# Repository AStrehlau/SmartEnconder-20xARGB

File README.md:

# SmartEncoder-20xARGB

This "SmartEncoder" uses 20 adressable LEDs (SK6805-EC15 or potentially XL-1615RGBC-WS2812B) to visualize the set point of the encoder. The SmartEncoder boasts WiFi and Bluetooth capability using the ESP32, which makes it viable for Smart Home and PC control applications.<br>
It should be noted that stock Windows does not normally have the capability to send the current volume level over BT, which is why a PC side software to take care of that will be uploaded  in the future for use as a BT PC volume knob.

## Hardware

You can directly order the three PCBs needed for this project using the Gerber files (generated for JLCPCB but likely to work with most common providers) or modify the PCB files at your discretion and generate new Gerber files.

Each of the three PCBs have to be completely assembled before they can be stacked in the correct order using the 3D printed spacers and either wire or very long headers. For the assembly of the Top/LED PCB it is recommended if not necessary to order a stencil with the PCBs. The other PCBs can be assembled without one if so desired.

There is a complete BOM (except the very long headers/wire and M3x25m screws!) for all three PCBs and an interactive BOM for the PCB with the ESP32 on it. There is no ibom for the other two PCBs since every capacitor used on them is 100nF, every resistor on the encoder PCB is 10k and the one resistor on the LED PCB is 330R as can be seen in the schematics.<br>
The EMI filter on the ESP32 PCB (L1, L2 and C4) can be left out and Jumper JP1 soldered instead, although it is not recommended. Doing this has no effect on the functionality.<br>
Especially if you don't plan on running intensive animations on the LEDs the 20 bypass capacitors are definitely overkill (even though the datasheet might disagree). If you want to save on parts/ time spent placing them you can just place C14, C15 and C16 which was more than enough in my testing even just one of them might work for you.

## 3D printed case

Thanks to [Nedos on Thingiverse](https://www.thingiverse.com/thing:6506406) designing a case including two knob versions for you to choose from and anti-bleed part for this project you can simply download the files and print them.<br>
The holes in the knob are meant to be filled with regular 1.75mm diameter transparent filament and either both surfaces cut flush using a side cutter or even sanded down for a better look.<br>
The anti-bleed part can simply be put on the LEDs making sure not to damage them.<br>
For assembly you only need the printed parts including spacers and M3x25mm screws, preferably with a flat underside.

## Software 

Because of layout reasons the LEDs have to be addressed in the opposite than expected order (LED number on the silkscreen is correct) which can result in longer code depending on the application.

There is a demo code for the LEDs which is just a slightly modified version of the Adafruit NEOPIXEL "strandtest" example to check if the LEDs are soldered correctly and undamaged as well as to give you a nice lightshow as can be seen at the top.<br>
This code can be flashed onto the ESP32 using the Arduino IDE.

Also available is a ESPHome configuration to integrate the SmartEncoder into HomeAssistant.

WIP: Code for ESP and PC to communicate via Serial over Bluetooth to use as a volume knob with accurate volume display on the SmartEncoder side

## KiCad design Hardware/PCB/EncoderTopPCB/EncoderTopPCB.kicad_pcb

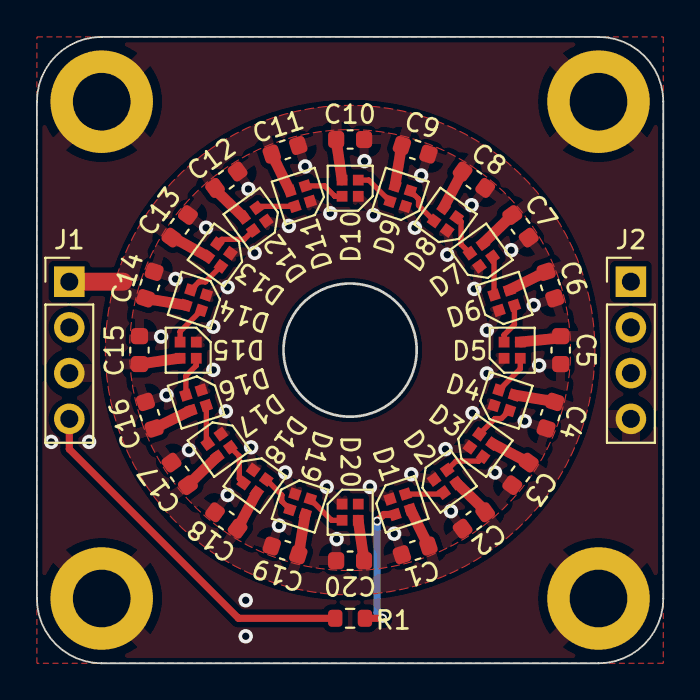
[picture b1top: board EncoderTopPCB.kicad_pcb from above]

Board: 2 copper layers, 34.8 x 34.8 mm, 47 parts (0 on the bottom side), 23 nets.

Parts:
C1, C2, C3, C4, C5, C6, C7, C8, C9, C10, C11, C12, C13, C14, C15, C16, C17, C18, C19, C20: 10V/100nF/X7R; C_0603_1608Metric
D1, D2, D3, D4, D5, D6, D7, D8, D9, D10, D11, D12, D13, D14, D15, D16, D17, D18, D19, D20: SK6805; SK6805-EC15
H1, H2, H3, H4: DNP; MountingHole_3.2mm_M3_ISO7380_Pad
J1, J2: DNP; PinHeader_1x04_P2.54mm_Vertical
R1: 330R; R_0603_1608Metric

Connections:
+5V: C1.1, C2.1, C3.1, C4.1, C5.1, C6.1, C7.1, C8.1, C9.1, C10.1, C11.1, C12.1, C13.1, C14.1, C15.1, C16.1, C17.1, C18.1, C19.1, C20.1, D1.2 (VDD), D2.2 (VDD), D3.2 (VDD), D4.2 (VDD), D5.2 (VDD), D6.2 (VDD), D7.2 (VDD), D8.2 (VDD), D9.2 (VDD), D10.2 (VDD), D11.2 (VDD), D12.2 (VDD), D13.2 (VDD), D14.2 (VDD), D15.2 (VDD), D16.2 (VDD), D17.2 (VDD), D18.2 (VDD), D19.2 (VDD), D20.2 (VDD), J1.1
GND: C1.2, C2.2, C3.2, C4.2, C5.2, C6.2, C7.2, C8.2, C9.2, C10.2, C11.2, C12.2, C13.2, C14.2, C15.2, C16.2, C17.2, C18.2, C19.2, C20.2, D1.4 (VSS), D2.4 (VSS), D3.4 (VSS), D4.4 (VSS), D5.4 (VSS), D6.4 (VSS), D7.4 (VSS), D8.4 (VSS), D9.4 (VSS), D10.4 (VSS), D11.4 (VSS), D12.4 (VSS), D13.4 (VSS), D14.4 (VSS), D15.4 (VSS), D16.4 (VSS), D17.4 (VSS), D18.4 (VSS), D19.4 (VSS), D20.4 (VSS), H1.1, H2.1, H3.1, H4.1, J1.3, J2.4
IO3: J1.4, R1.1
unnamed: D1.1 (DIN), R1.2
unnamed: D1.3 (DOUT), D2.1 (DIN)
unnamed: D2.3 (DOUT), D3.1 (DIN)
unnamed: D3.3 (DOUT), D4.1 (DIN)
unnamed: D4.3 (DOUT), D5.1 (DIN)
unnamed: D5.3 (DOUT), D6.1 (DIN)
unnamed: D6.3 (DOUT), D7.1 (DIN)
unnamed: D7.3 (DOUT), D8.1 (DIN)
unnamed: D8.3 (DOUT), D9.1 (DIN)
unnamed: D9.3 (DOUT), D10.1 (DIN)
unnamed: D10.3 (DOUT), D11.1 (DIN)
unnamed: D11.3 (DOUT), D12.1 (DIN)
unnamed: D12.3 (DOUT), D13.1 (DIN)
unnamed: D13.3 (DOUT), D14.1 (DIN)
unnamed: D14.3 (DOUT), D15.1 (DIN)
unnamed: D15.3 (DOUT), D16.1 (DIN)
unnamed: D16.3 (DOUT), D17.1 (DIN)
unnamed: D17.3 (DOUT), D18.1 (DIN)
unnamed: D18.3 (DOUT), D19.1 (DIN)
unnamed: D19.3 (DOUT), D20.1 (DIN)

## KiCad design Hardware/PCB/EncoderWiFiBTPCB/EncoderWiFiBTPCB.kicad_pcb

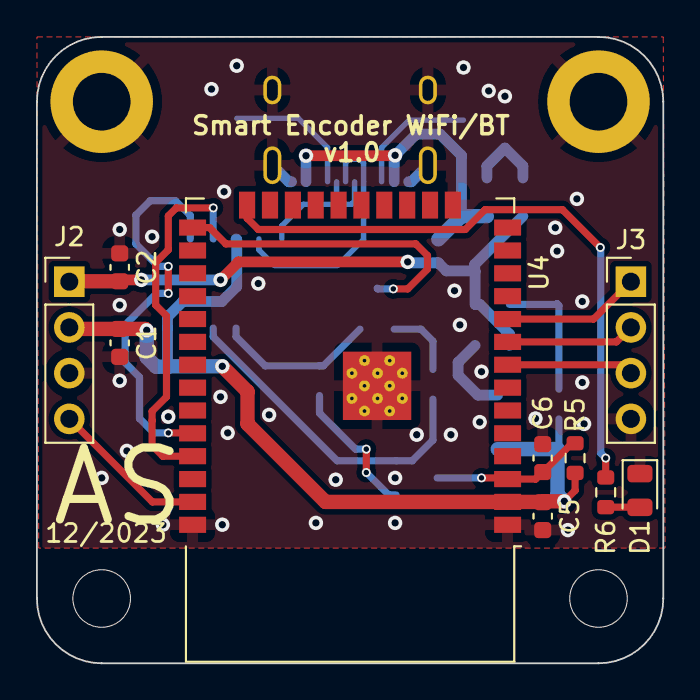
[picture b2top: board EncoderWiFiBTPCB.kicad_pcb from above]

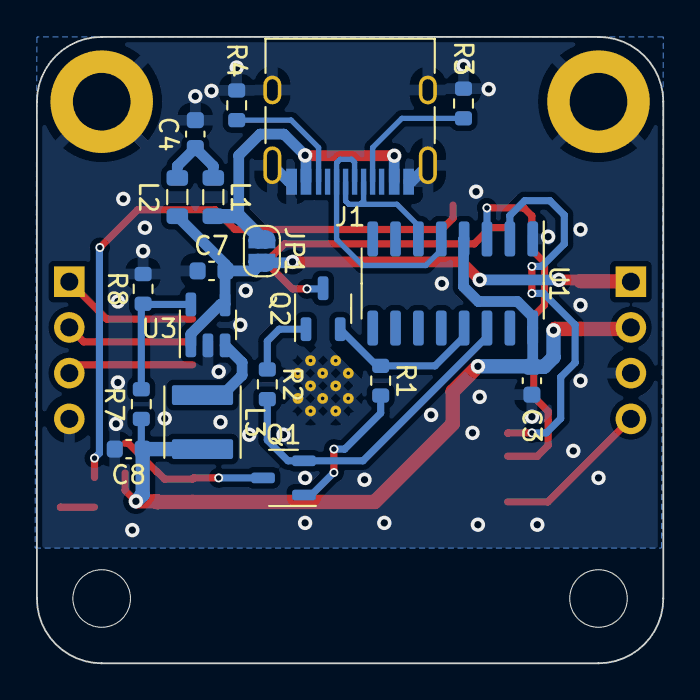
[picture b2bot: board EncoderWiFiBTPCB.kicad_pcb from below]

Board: 2 copper layers, 34.8 x 34.8 mm, 33 parts (19 on the bottom side), 25 nets.

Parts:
C1, C2, C4: 1uF/25V/X5R; C_0603_1608Metric
C3, C5, C6: 100nF/10V/X7R; C_0603_1608Metric
C7, C8: 22uF/10V/X5R; C_0603_1608Metric
D1: BLUE; LED_0805_2012Metric
H1, H2: MountingHole_Pad; MountingHole_3.2mm_M3_ISO7380_Pad
H3, H4: MountingHole; MountingHole_3.2mm_M3_ISO7380
J1: USB_C_Receptacle_USB2.0; USB_C_Receptacle_HRO_TYPE-C-31-M-12
J2, J3: Conn_01x04_Pin; PinHeader_1x04_P2.54mm_Vertical
JP1: SolderJumper_2_Open; SolderJumper-2_P1.3mm_Open_RoundedPad1.0x1.5mm
L1, L2: WLBD2012HCU601TH; L_0805_2012Metric
L3: 2.2uH; L_Abracon_ASPI-4030S
Q1, Q2: MMBT4401; SOT-23-3
R1, R2, R5: 10k; R_0603_1608Metric
R3, R4: 5.1k; R_0603_1608Metric
R6: 1k; R_0603_1608Metric
R7: 68k; R_0603_1608Metric
R8: 15k; R_0603_1608Metric
U1: CH340C; SOIC-16_3.9x9.9mm_P1.27mm
U3: M3406; SOT-23-5
U4: ESP32-WROOM-32D

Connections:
+3V3: C1.1, C3.1, C5.2, C8.1, J2.2, L3.2, R5.2, R7.1, U1.4 (V3), U1.16 (VCC), U4.2 (VDD)
+5V: C2.1, C7.1, J2.1, JP1.2 (B), L2.2, U3.1 (RUN), U3.4 (VIN)
D+: J1.A6 (D+), J1.B6 (D+), U1.5 (UD+)
D-: J1.A7 (D-), J1.B7 (D-), U1.6 (UD-)
ENCODER_A: J3.2, U4.9 (IO33)
ENCODER_B: J3.3, U4.8 (IO32)
ENCODER_BTN: J3.1, U4.10 (IO25)
GND: C1.2, C2.2, C3.2, C4.2, C5.1, C6.1, C7.2, C8.2, D1.1 (K), H1.1, H2.1, J1.A1 (GND), J1.A12 (GND), J1.B1 (GND), J1.B12 (GND), J1.S1 (SHIELD), J2.3, J3.4, R3.2, R4.2, R8.2, U1.1 (GND), U3.2 (GND), U4.1 (GND), U4.15 (GND), U4.38 (GND), U4.39 (GND)
IO23: J2.4, U4.37 (IO23)
unnamed: C4.1, L1.2, L2.1
unnamed: D1.2 (A), R6.1
unnamed: J1.A5 (CC1), R3.1
unnamed: J1.B5 (CC2), R4.1
unnamed: J1.A4 (VBUS), J1.A9 (VBUS), J1.B4 (VBUS), J1.B9 (VBUS), JP1.1 (A), L1.1
unnamed: Q1.1 (B), R1.2
unnamed: Q1.2 (E), R2.1, U1.14 (~RTS)
unnamed: Q2.1 (B), R2.2
unnamed: Q2.2 (E), R1.1, U1.13 (~DTR)
unnamed: R7.2, R8.1, U3.5 (FB)
unnamed: L3.1, U3.3 (SW)
unnamed: R6.2, U4.24 (IO2)
RX0 (Programming): U1.2 (TXD), U4.34 (RXD0/IO3)
TX0 (Programming): U1.3 (RXD), U4.35 (TXD0/IO1)
~BOOTMODE: Q2.3 (C), U4.25 (IO0)
~RST: C6.2, Q1.3 (C), R5.1, U4.3 (EN)

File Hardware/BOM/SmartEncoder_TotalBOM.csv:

Id,Footprint,Quantity,Designation,Supplier and ref,
1,R_0603_1608Metric,6,10k,,
2,C_0603_1608Metric,3,1uF/10V/X5R,,
3,C_0603_1608Metric,24,100nF/10V/X7R,,
4,ESP32-WROOM-32D,1,ESP32-WROOM-32D,,NOTE: any ESP32-WROOM-32x works
5,R_0603_1608Metric,1,1k,,
6,LED_0805_2012Metric,1,BLUE,,
7,C_0603_1608Metric,2,22uF/10V/X5R,,
8,USB_C_Receptacle_HRO_TYPE-C-31-M-12,1,USB_C_Receptacle_USB2.0,SHOU HAN TYPE-C 16PIN 2MD(073),
9,SolderJumper-2_P1.3mm_Open_RoundedPad1.0x1.5mm,1,SolderJumper_2_Open,,
10,SOT-23-3,2,MMBT4401,,
11,R_0603_1608Metric,1,15k,,
12,L_0805_2012Metric,2,WLBD2012HCU601TH,WLBD2012HCU601TH or SBH2012S601NSP,SBH2012S601NSP is cheaper
13,R_0603_1608Metric,1,68k,,
14,SOT-23-5,1,M3406,,
15,L_Abracon_ASPI-4030S,1,2.2uH,SWPA4030S2R2,
16,SOIC-16_3.9x9.9mm_P1.27mm,1,CH340C,,
17,R_0603_1608Metric,2,5.1k,,
18,RotaryEncoder_Alps_EC11E-Switch_Vertical_H20mm,1,RotaryEncoder_Switch,,EC11 20mm „plum handle“
19,SK6805-EC15,20,SK6805-EC15,,NOTE: XL-1615RGBC-WS2812B !might! Work too and is cheaper
20,R_0603_1608Metric,1,330R,,

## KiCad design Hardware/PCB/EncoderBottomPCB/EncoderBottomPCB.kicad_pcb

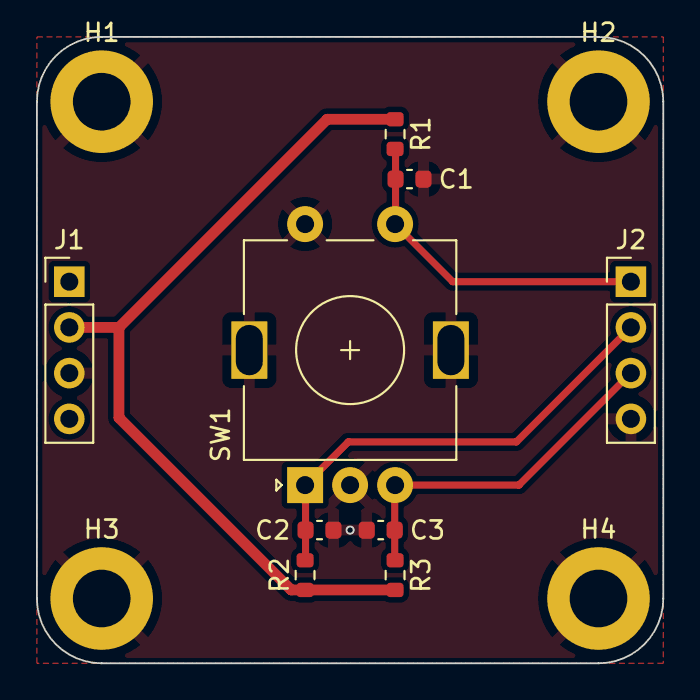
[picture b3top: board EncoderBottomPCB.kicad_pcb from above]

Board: 2 copper layers, 34.8 x 34.8 mm, 13 parts (0 on the bottom side), 5 nets.

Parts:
C1, C2, C3: 100nF/10V/X7R; C_0603_1608Metric
H1, H2, H3, H4: MountingHole_Pad; MountingHole_3.2mm_M3_ISO7380_Pad
J1, J2: Conn_01x04_Pin; PinHeader_1x04_P2.54mm_Vertical
R1, R2, R3: 10k; R_0603_1608Metric
SW1: RotaryEncoder_Switch; RotaryEncoder_Alps_EC11E-Switch_Vertical_H20mm

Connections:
+3V3: J1.2, R1.1, R2.1, R3.2
ENCODER_A: C2.2, J2.2, R2.2, SW1.A
ENCODER_B: C3.2, J2.3, R3.1, SW1.B
ENCODER_BTN: C1.2, J2.1, R1.2, SW1.S1
GND: C1.1, C2.1, C3.1, H1.1, H2.1, H3.1, H4.1, J1.3, J2.4, SW1.C, SW1.MP, SW1.S2

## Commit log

2024-02-27 SmartEncoder
2024-02-27 Create LICENSE
2024-02-27 Update LICENSE
2024-02-27 Correct 3D file names
2024-02-27 Changed link to point to Thingiverse project
